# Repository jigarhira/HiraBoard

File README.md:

# HiraBoard
Custom keyboard design based on STM32 and QMK

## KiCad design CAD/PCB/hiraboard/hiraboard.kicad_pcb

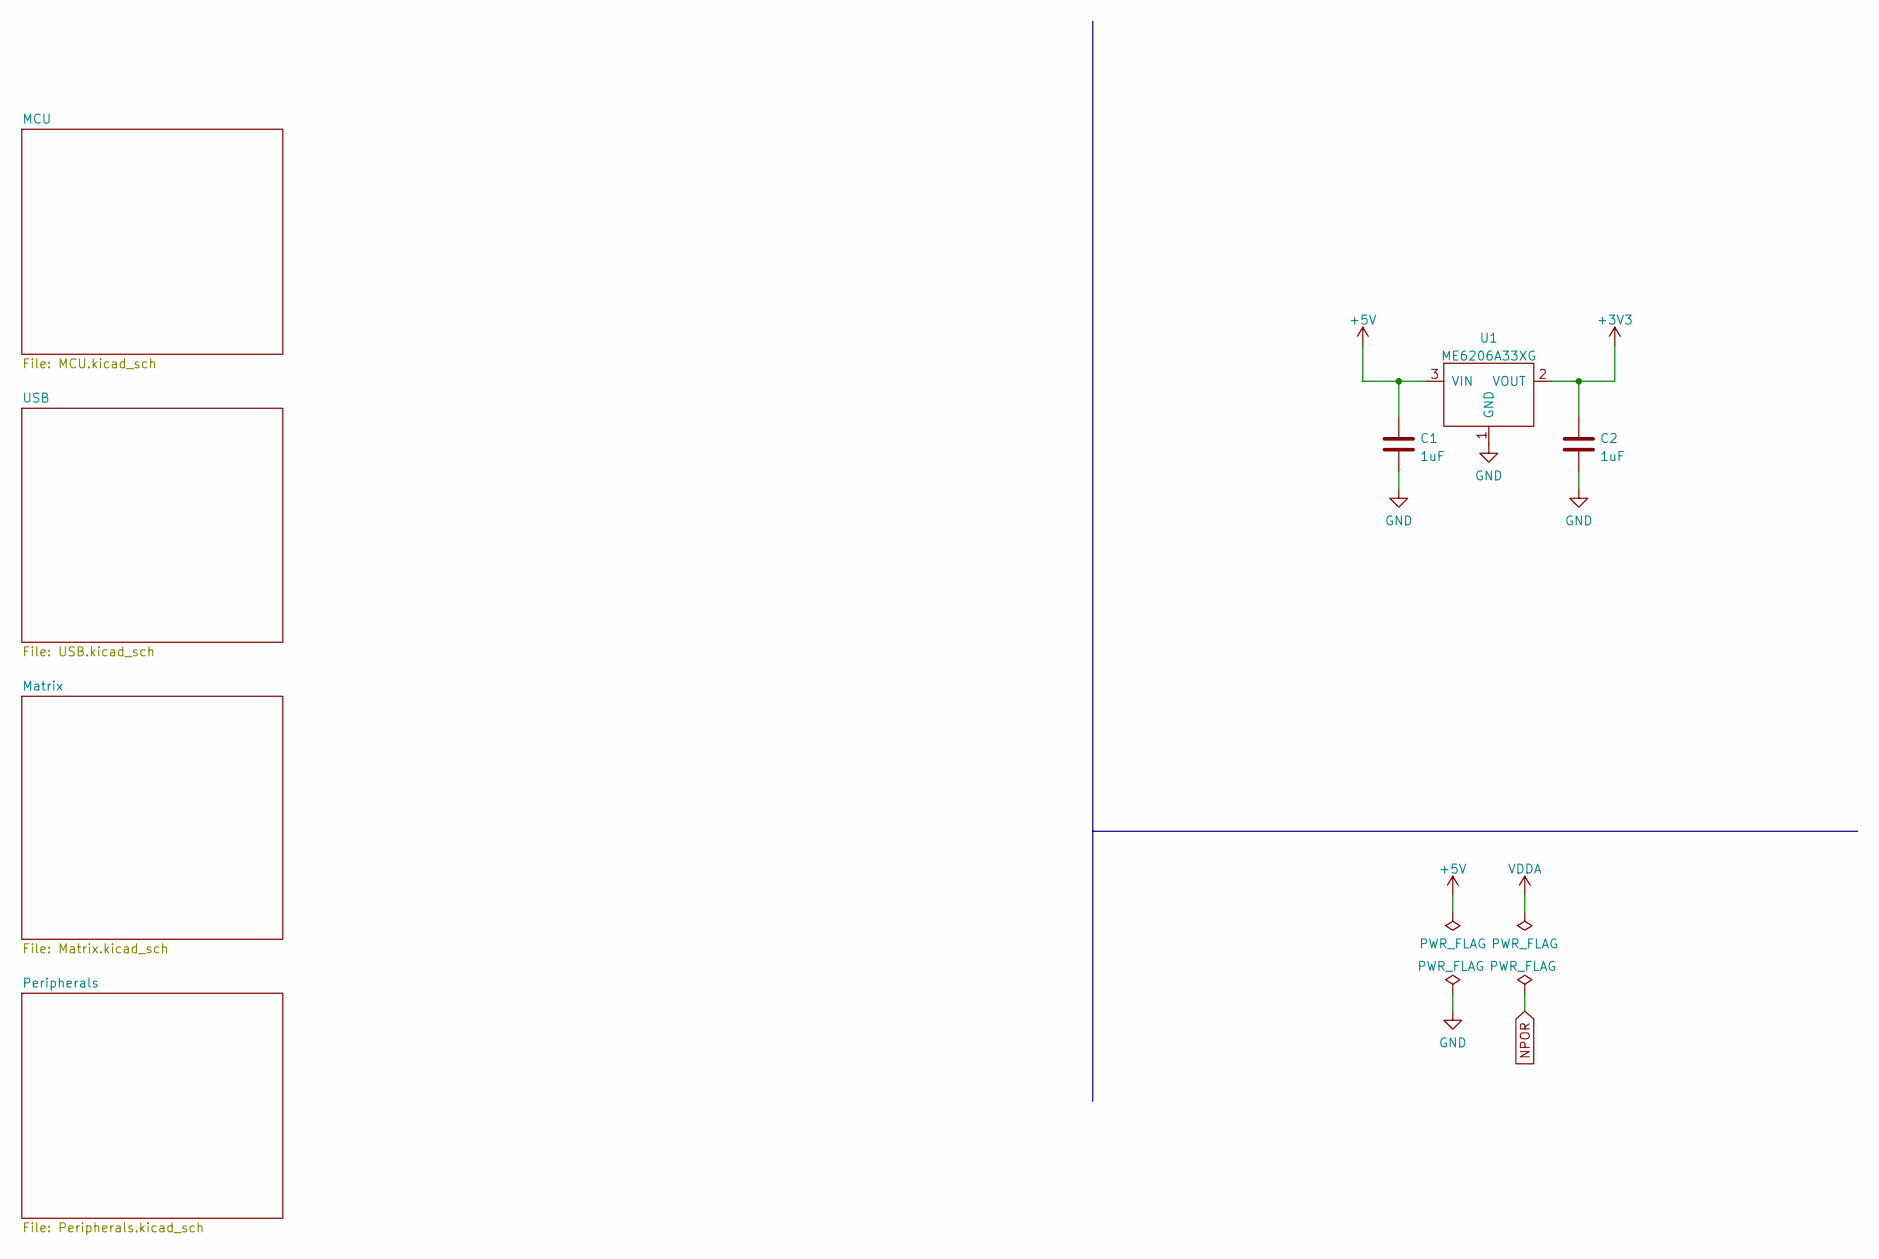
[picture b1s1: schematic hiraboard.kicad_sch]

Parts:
C1, C2: 1uF; C_0603_1608Metric
U1: ME6206A33XG; SOT-23

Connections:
+5V: C1.1, U1.3 (VIN); also elsewhere on the board
GND: C1.2, C2.2, U1.1 (GND); also elsewhere on the board

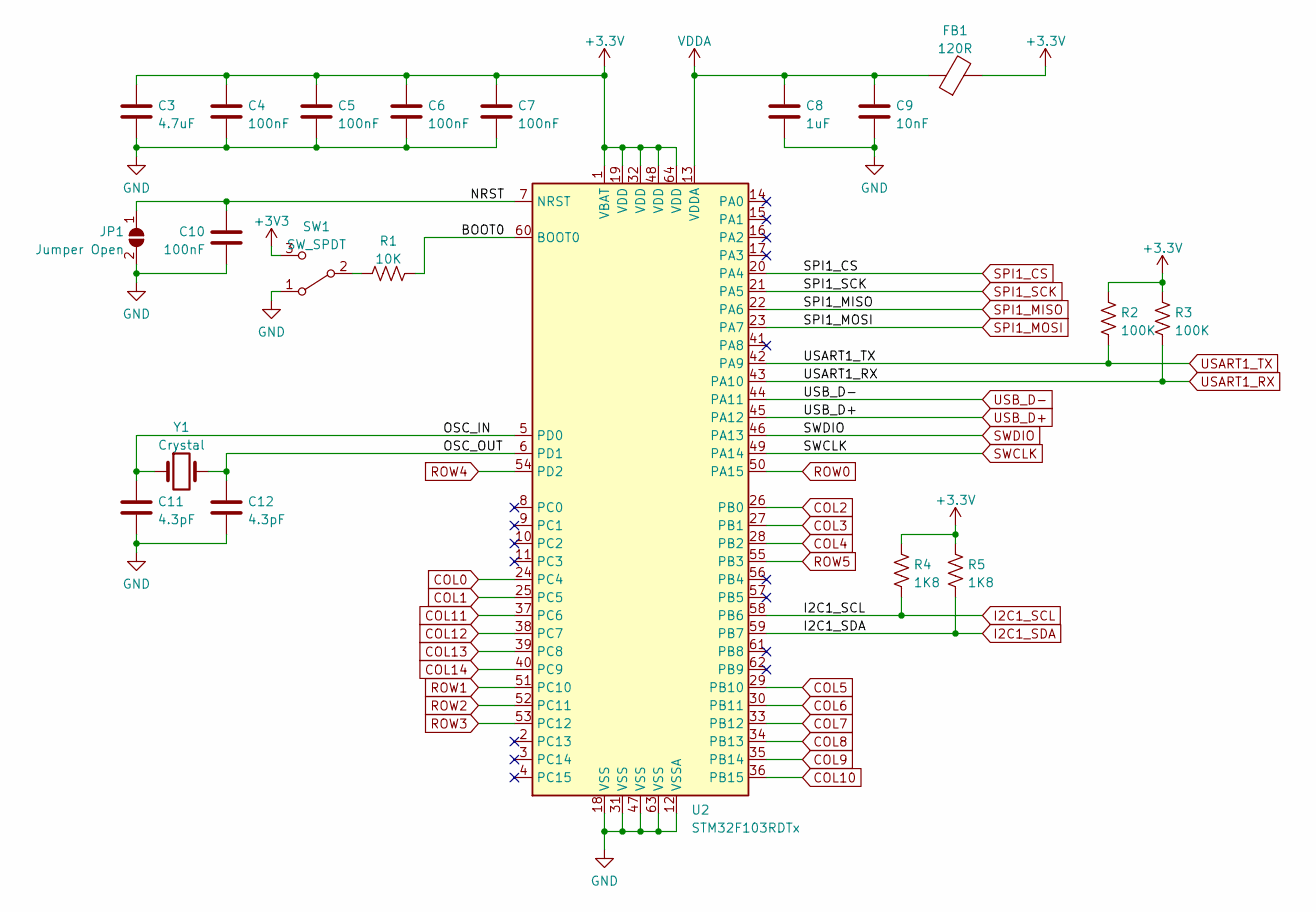
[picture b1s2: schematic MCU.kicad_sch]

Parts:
C3: 4.7uF; C_0603_1608Metric
C4, C5, C6, C7, C10: 100nF; C_0603_1608Metric
C8: 1uF; C_0603_1608Metric
C9: 10nF; C_0603_1608Metric
C11, C12: 4.3pF; C_0603_1608Metric
FB1: 120R; R_0603_1608Metric
JP1: Jumper Open; SolderJumper-2_P1.3mm_Open_RoundedPad1.0x1.5mm
R1: 10K; R_0603_1608Metric
R2, R3: 100K; R_0603_1608Metric
R4, R5: 1K8; R_0603_1608Metric
SW1: SW_SPDT
U2: STM32F103RDTx; LQFP-64_10x10mm_P0.5mm
Y1: Crystal

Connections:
/MCU/BOOT0: R1.2, U2.60 (BOOT0)
/MCU/NRST: C10.1, JP1.1 (A), U2.7 (NRST)
/MCU/OSC_IN: C11.1, U2.5 (PD0), Y1.1
/MCU/OSC_OUT: C12.1, U2.6 (PD1), Y1.2
COL0: U2.24 (PC4); also elsewhere on the board
COL1: U2.25 (PC5); also elsewhere on the board
COL2: U2.26 (PB0); also elsewhere on the board
COL3: U2.27 (PB1); also elsewhere on the board
COL4: U2.28 (PB2); also elsewhere on the board
COL5: U2.29 (PB10); also elsewhere on the board
COL6: U2.30 (PB11); also elsewhere on the board
COL7: U2.33 (PB12); also elsewhere on the board
COL8: U2.34 (PB13); also elsewhere on the board
COL9: U2.35 (PB14); also elsewhere on the board
COL10: U2.36 (PB15); also elsewhere on the board
COL11: U2.37 (PC6); also elsewhere on the board
COL12: U2.38 (PC7); also elsewhere on the board
COL13: U2.39 (PC8); also elsewhere on the board
COL14: U2.40 (PC9); also elsewhere on the board
GND: C3.2, C4.2, C5.2, C6.2, C7.2, C8.2, C9.2, C10.2, C11.2, C12.2, JP1.2 (B), SW1.1 (A), U2.12 (VSSA), U2.18 (VSS), U2.31 (VSS), U2.47 (VSS), U2.63 (VSS); also elsewhere on the board
I2C1_SCL: R4.2, U2.58 (PB6); also elsewhere on the board
I2C1_SDA: R5.2, U2.59 (PB7); also elsewhere on the board
unnamed: R1.1, SW1.2 (B)
ROW0: U2.50 (PA15); also elsewhere on the board
ROW1: U2.51 (PC10); also elsewhere on the board
ROW2: U2.52 (PC11); also elsewhere on the board
ROW3: U2.53 (PC12); also elsewhere on the board
ROW4: U2.54 (PD2); also elsewhere on the board
ROW5: U2.55 (PB3); also elsewhere on the board
SPI1_CS: U2.20 (PA4); also elsewhere on the board
SPI1_MISO: U2.22 (PA6); also elsewhere on the board
SPI1_MOSI: U2.23 (PA7); also elsewhere on the board
SPI1_SCK: U2.21 (PA5); also elsewhere on the board
SWCLK: U2.49 (PA14); also elsewhere on the board
SWDIO: U2.46 (PA13); also elsewhere on the board
USART1_RX: R3.2, U2.43 (PA10); also elsewhere on the board
USART1_TX: R2.2, U2.42 (PA9); also elsewhere on the board
USB_D+: U2.45 (PA12); also elsewhere on the board
USB_D-: U2.44 (PA11); also elsewhere on the board
VDDA: C8.1, C9.1, FB1.1, U2.13 (VDDA)

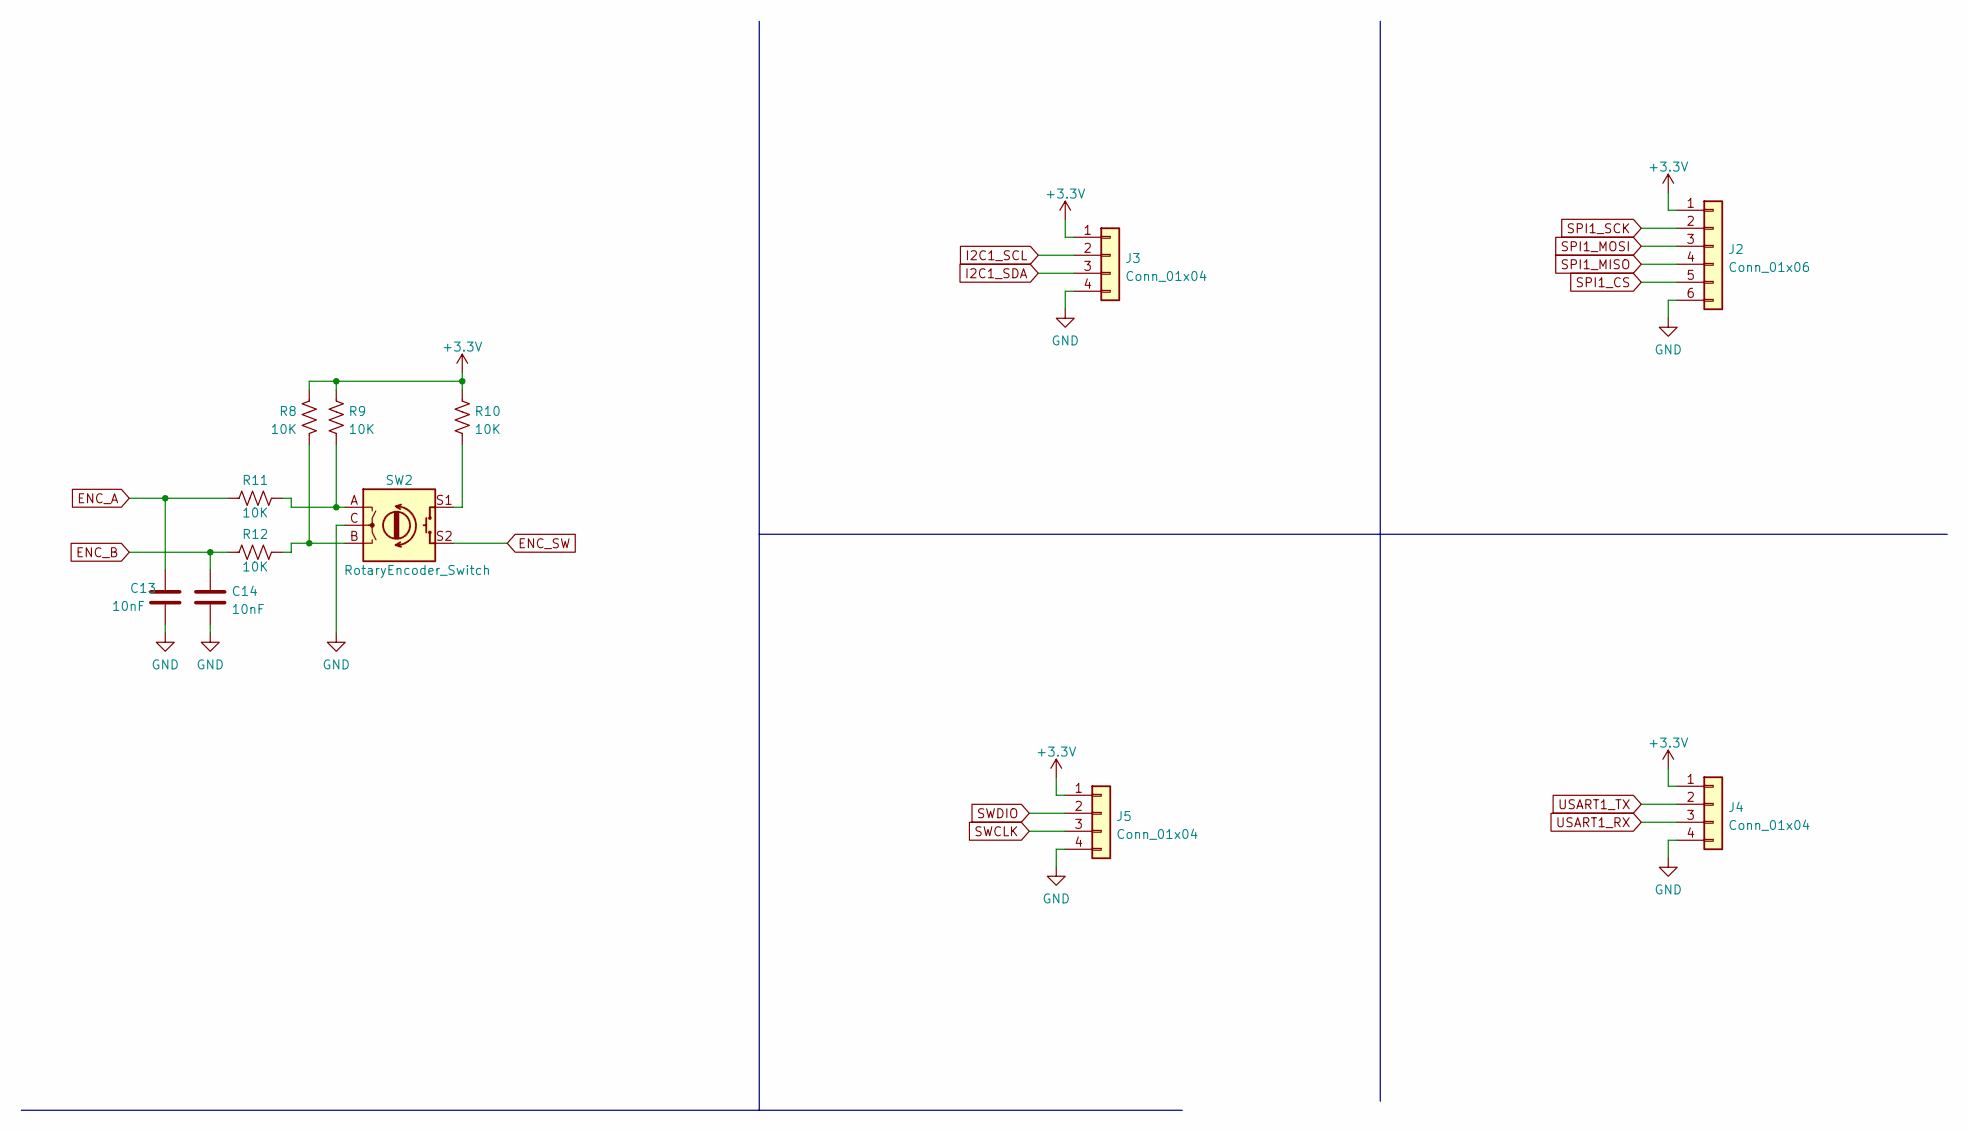
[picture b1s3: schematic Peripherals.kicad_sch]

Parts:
C13, C14: 10nF; C_0603_1608Metric
J2: Conn_01x06; PinSocket_1x06_P2.54mm_Horizontal
J3, J4, J5: Conn_01x04; PinSocket_1x04_P2.54mm_Horizontal
R8, R9, R10, R11, R12: 10K; R_0603_1608Metric
SW2: RotaryEncoder_Switch; PEC12R-4xxxF-Sxxxx

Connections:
ENC_A: C13.1, R11.2
ENC_B: C14.1, R12.2
ENC_SW: SW2.S2
GND: C13.2, C14.2, J2.6, J3.4, J4.4, J5.4, SW2.C; also elsewhere on the board
I2C1_SCL: J3.2; also elsewhere on the board
I2C1_SDA: J3.3; also elsewhere on the board
unnamed: R10.2, SW2.S1
unnamed: R9.2, R11.1, SW2.A
unnamed: R8.1, R12.1, SW2.B
SPI1_CS: J2.5; also elsewhere on the board
SPI1_MISO: J2.4; also elsewhere on the board
SPI1_MOSI: J2.3; also elsewhere on the board
SPI1_SCK: J2.2; also elsewhere on the board
SWCLK: J5.3; also elsewhere on the board
SWDIO: J5.2; also elsewhere on the board
USART1_RX: J4.3; also elsewhere on the board
USART1_TX: J4.2; also elsewhere on the board

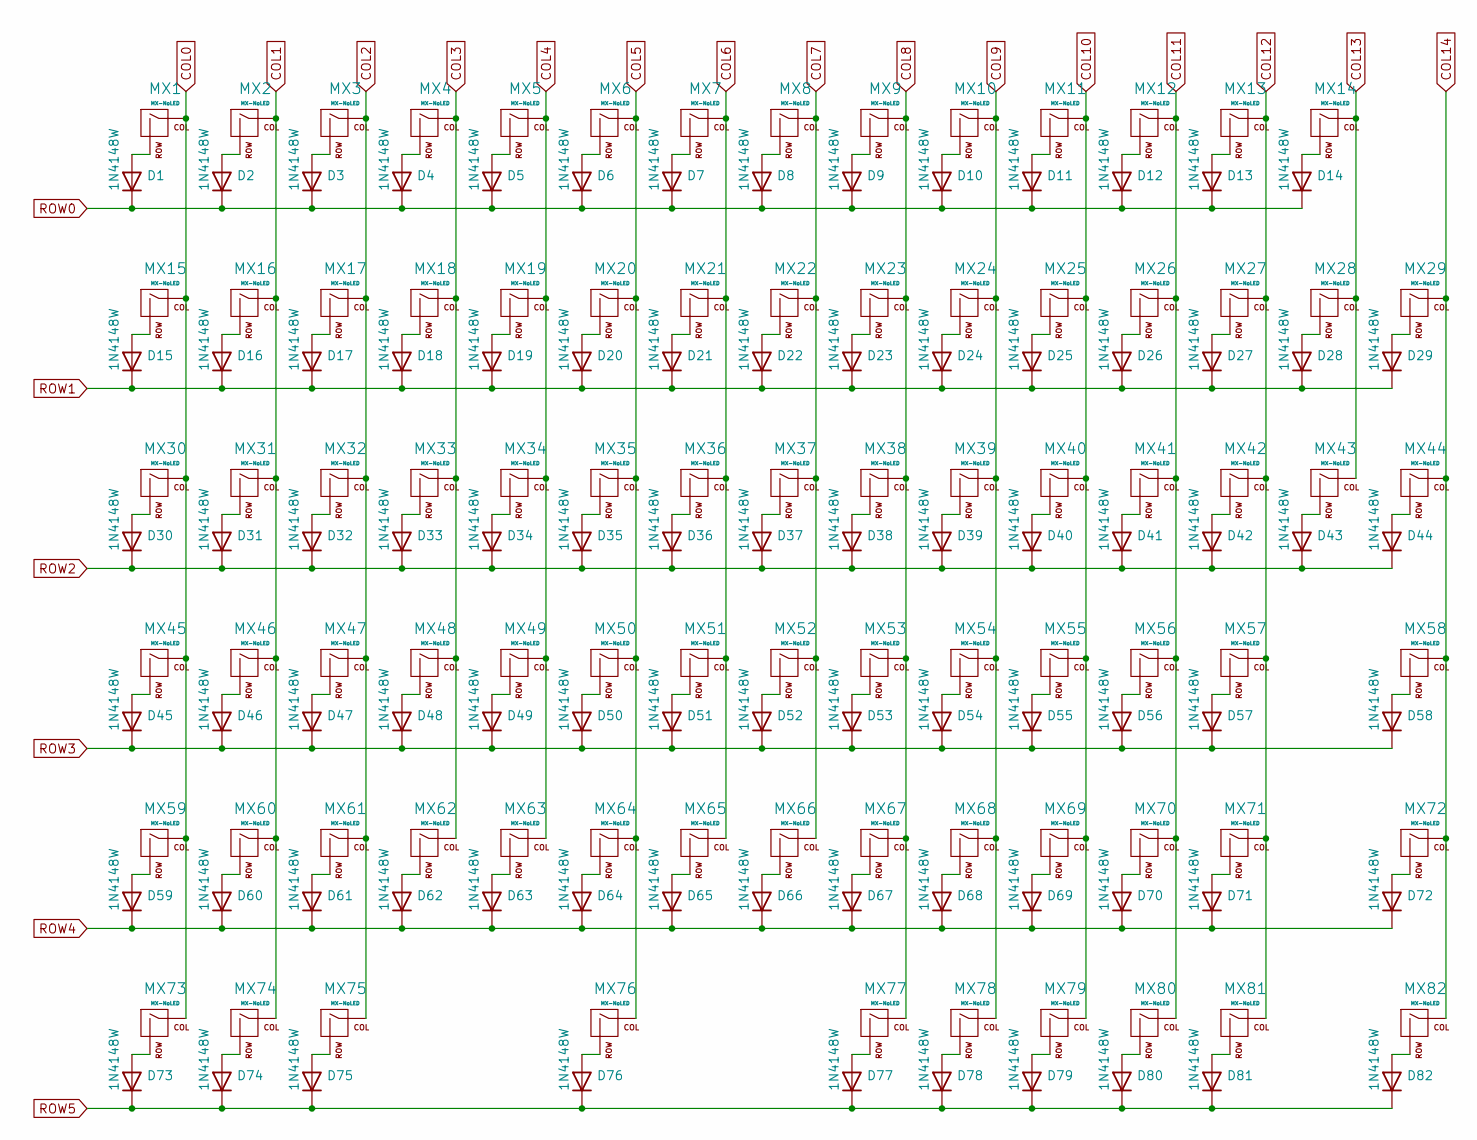
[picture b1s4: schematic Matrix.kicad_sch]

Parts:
D1, D2, D3, D4, D5, D6, D7, D8, D9, D10, D11, D12, D13, D14, D15, D16, D17, D18, D19, D20, D21, D22, D23, D24, D25, D26, D27, D28, D29, D30, D31, D32, D33, D34, D35, D36, D37, D38, D39, D40, D41, D42, D43, D44, D45, D46, D47, D48, D49, D50, D51, D52, D53, D54, D55, D56, D57, D58, D59, D60, D61, D62, D63, D64, D65, D66, D67, D68, D69, D70, D71, D72, D73, D74, D75, D76, D77, D78, D79, D80, D81, D82: 1N4148W; D_SOD-123
MX1, MX2, MX3, MX4, MX5, MX6, MX7, MX8, MX9, MX10, MX11, MX12, MX13, MX14, MX15, MX16, MX17, MX18, MX19, MX20, MX21, MX22, MX23, MX24, MX25, MX26, MX27, MX29, MX31, MX32, MX33, MX34, MX35, MX36, MX37, MX38, MX39, MX40, MX41, MX42, MX44, MX46, MX47, MX48, MX49, MX50, MX51, MX52, MX53, MX54, MX55, MX56, MX58, MX60, MX61, MX62, MX63, MX64, MX65, MX66, MX67, MX68, MX69, MX71, MX72, MX77, MX78, MX79, MX80, MX81, MX82: MX-NoLED; MXOnly-1U-Hotswap
MX28: MX-NoLED; MXOnly-2U-Hotswap
MX30, MX43: MX-NoLED; MXOnly-1.5U-Hotswap
MX45, MX70: MX-NoLED; MXOnly-1.75U-Hotswap
MX57, MX59: MX-NoLED; MXOnly-2.25U-Hotswap
MX73, MX74, MX75: MX-NoLED; MXOnly-1.25U-Hotswap
MX76: MX-NoLED; MXOnly-6.25U-Hotswap

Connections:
COL0: MX1.1 (COL), MX15.1 (COL), MX30.1 (COL), MX45.1 (COL), MX59.1 (COL), MX73.1 (COL); also elsewhere on the board
COL1: MX2.1 (COL), MX16.1 (COL), MX31.1 (COL), MX46.1 (COL), MX60.1 (COL), MX74.1 (COL); also elsewhere on the board
COL2: MX3.1 (COL), MX17.1 (COL), MX32.1 (COL), MX47.1 (COL), MX61.1 (COL), MX75.1 (COL); also elsewhere on the board
COL3: MX4.1 (COL), MX18.1 (COL), MX33.1 (COL), MX48.1 (COL), MX62.1 (COL); also elsewhere on the board
COL4: MX5.1 (COL), MX19.1 (COL), MX34.1 (COL), MX49.1 (COL), MX63.1 (COL); also elsewhere on the board
COL5: MX6.1 (COL), MX20.1 (COL), MX35.1 (COL), MX50.1 (COL), MX64.1 (COL), MX76.1 (COL); also elsewhere on the board
COL6: MX7.1 (COL), MX21.1 (COL), MX36.1 (COL), MX51.1 (COL), MX65.1 (COL); also elsewhere on the board
COL7: MX8.1 (COL), MX22.1 (COL), MX37.1 (COL), MX52.1 (COL), MX66.1 (COL); also elsewhere on the board
COL8: MX9.1 (COL), MX23.1 (COL), MX38.1 (COL), MX53.1 (COL), MX67.1 (COL), MX77.1 (COL); also elsewhere on the board
COL9: MX10.1 (COL), MX24.1 (COL), MX39.1 (COL), MX54.1 (COL), MX68.1 (COL), MX78.1 (COL); also elsewhere on the board
COL10: MX11.1 (COL), MX25.1 (COL), MX40.1 (COL), MX55.1 (COL), MX69.1 (COL), MX79.1 (COL); also elsewhere on the board
COL11: MX12.1 (COL), MX26.1 (COL), MX41.1 (COL), MX56.1 (COL), MX70.1 (COL), MX80.1 (COL); also elsewhere on the board
COL12: MX13.1 (COL), MX27.1 (COL), MX42.1 (COL), MX57.1 (COL), MX71.1 (COL), MX81.1 (COL); also elsewhere on the board
COL13: MX14.1 (COL), MX28.1 (COL), MX43.1 (COL); also elsewhere on the board
COL14: MX29.1 (COL), MX44.1 (COL), MX58.1 (COL), MX72.1 (COL), MX82.1 (COL); also elsewhere on the board
unnamed: D1.2 (A), MX1.2 (ROW)
unnamed: D2.2 (A), MX2.2 (ROW)
unnamed: D3.2 (A), MX3.2 (ROW)
unnamed: D4.2 (A), MX4.2 (ROW)
unnamed: D5.2 (A), MX5.2 (ROW)
unnamed: D6.2 (A), MX6.2 (ROW)
unnamed: D7.2 (A), MX7.2 (ROW)
unnamed: D8.2 (A), MX8.2 (ROW)
unnamed: D9.2 (A), MX9.2 (ROW)
unnamed: D10.2 (A), MX10.2 (ROW)
unnamed: D11.2 (A), MX11.2 (ROW)
unnamed: D12.2 (A), MX12.2 (ROW)
unnamed: D13.2 (A), MX13.2 (ROW)
unnamed: D14.2 (A), MX14.2 (ROW)
unnamed: D15.2 (A), MX15.2 (ROW)
unnamed: D16.2 (A), MX16.2 (ROW)
unnamed: D17.2 (A), MX17.2 (ROW)
unnamed: D18.2 (A), MX18.2 (ROW)
unnamed: D19.2 (A), MX19.2 (ROW)
unnamed: D20.2 (A), MX20.2 (ROW)
unnamed: D21.2 (A), MX21.2 (ROW)
unnamed: D22.2 (A), MX22.2 (ROW)
unnamed: D23.2 (A), MX23.2 (ROW)
unnamed: D24.2 (A), MX24.2 (ROW)
unnamed: D25.2 (A), MX25.2 (ROW)
unnamed: D26.2 (A), MX26.2 (ROW)
unnamed: D27.2 (A), MX27.2 (ROW)
unnamed: D28.2 (A), MX28.2 (ROW)
unnamed: D29.2 (A), MX29.2 (ROW)
unnamed: D30.2 (A), MX30.2 (ROW)
unnamed: D31.2 (A), MX31.2 (ROW)
unnamed: D32.2 (A), MX32.2 (ROW)
unnamed: D33.2 (A), MX33.2 (ROW)
unnamed: D34.2 (A), MX34.2 (ROW)
unnamed: D35.2 (A), MX35.2 (ROW)
unnamed: D36.2 (A), MX36.2 (ROW)
unnamed: D37.2 (A), MX37.2 (ROW)
unnamed: D38.2 (A), MX38.2 (ROW)
unnamed: D39.2 (A), MX39.2 (ROW)
unnamed: D40.2 (A), MX40.2 (ROW)
unnamed: D41.2 (A), MX41.2 (ROW)
unnamed: D42.2 (A), MX42.2 (ROW)
unnamed: D43.2 (A), MX43.2 (ROW)
unnamed: D44.2 (A), MX44.2 (ROW)
unnamed: D45.2 (A), MX45.2 (ROW)
unnamed: D46.2 (A), MX46.2 (ROW)
unnamed: D47.2 (A), MX47.2 (ROW)
unnamed: D48.2 (A), MX48.2 (ROW)
unnamed: D49.2 (A), MX49.2 (ROW)
unnamed: D50.2 (A), MX50.2 (ROW)
unnamed: D51.2 (A), MX51.2 (ROW)
unnamed: D52.2 (A), MX52.2 (ROW)
unnamed: D53.2 (A), MX53.2 (ROW)
unnamed: D54.2 (A), MX54.2 (ROW)
unnamed: D55.2 (A), MX55.2 (ROW)
unnamed: D56.2 (A), MX56.2 (ROW)
unnamed: D57.2 (A), MX57.2 (ROW)
unnamed: D58.2 (A), MX58.2 (ROW)
unnamed: D59.2 (A), MX59.2 (ROW)
unnamed: D60.2 (A), MX60.2 (ROW)
unnamed: D61.2 (A), MX61.2 (ROW)
unnamed: D62.2 (A), MX62.2 (ROW)
unnamed: D63.2 (A), MX63.2 (ROW)
unnamed: D64.2 (A), MX64.2 (ROW)
unnamed: D65.2 (A), MX65.2 (ROW)
unnamed: D66.2 (A), MX66.2 (ROW)
unnamed: D67.2 (A), MX67.2 (ROW)
unnamed: D68.2 (A), MX68.2 (ROW)
unnamed: D69.2 (A), MX69.2 (ROW)
unnamed: D70.2 (A), MX70.2 (ROW)
unnamed: D71.2 (A), MX71.2 (ROW)
unnamed: D72.2 (A), MX72.2 (ROW)
unnamed: D73.2 (A), MX73.2 (ROW)
unnamed: D74.2 (A), MX74.2 (ROW)
unnamed: D75.2 (A), MX75.2 (ROW)
unnamed: D76.2 (A), MX76.2 (ROW)
unnamed: D77.2 (A), MX77.2 (ROW)
unnamed: D78.2 (A), MX78.2 (ROW)
unnamed: D79.2 (A), MX79.2 (ROW)
unnamed: D80.2 (A), MX80.2 (ROW)
unnamed: D81.2 (A), MX81.2 (ROW)
unnamed: D82.2 (A), MX82.2 (ROW)
ROW0: D1.1 (K), D2.1 (K), D3.1 (K), D4.1 (K), D5.1 (K), D6.1 (K), D7.1 (K), D8.1 (K), D9.1 (K), D10.1 (K), D11.1 (K), D12.1 (K), D13.1 (K), D14.1 (K); also elsewhere on the board
ROW1: D15.1 (K), D16.1 (K), D17.1 (K), D18.1 (K), D19.1 (K), D20.1 (K), D21.1 (K), D22.1 (K), D23.1 (K), D24.1 (K), D25.1 (K), D26.1 (K), D27.1 (K), D28.1 (K), D29.1 (K); also elsewhere on the board
ROW2: D30.1 (K), D31.1 (K), D32.1 (K), D33.1 (K), D34.1 (K), D35.1 (K), D36.1 (K), D37.1 (K), D38.1 (K), D39.1 (K), D40.1 (K), D41.1 (K), D42.1 (K), D43.1 (K), D44.1 (K); also elsewhere on the board
ROW3: D45.1 (K), D46.1 (K), D47.1 (K), D48.1 (K), D49.1 (K), D50.1 (K), D51.1 (K), D52.1 (K), D53.1 (K), D54.1 (K), D55.1 (K), D56.1 (K), D57.1 (K), D58.1 (K); also elsewhere on the board
ROW4: D59.1 (K), D60.1 (K), D61.1 (K), D62.1 (K), D63.1 (K), D64.1 (K), D65.1 (K), D66.1 (K), D67.1 (K), D68.1 (K), D69.1 (K), D70.1 (K), D71.1 (K), D72.1 (K); also elsewhere on the board
ROW5: D73.1 (K), D74.1 (K), D75.1 (K), D76.1 (K), D77.1 (K), D78.1 (K), D79.1 (K), D80.1 (K), D81.1 (K), D82.1 (K); also elsewhere on the board

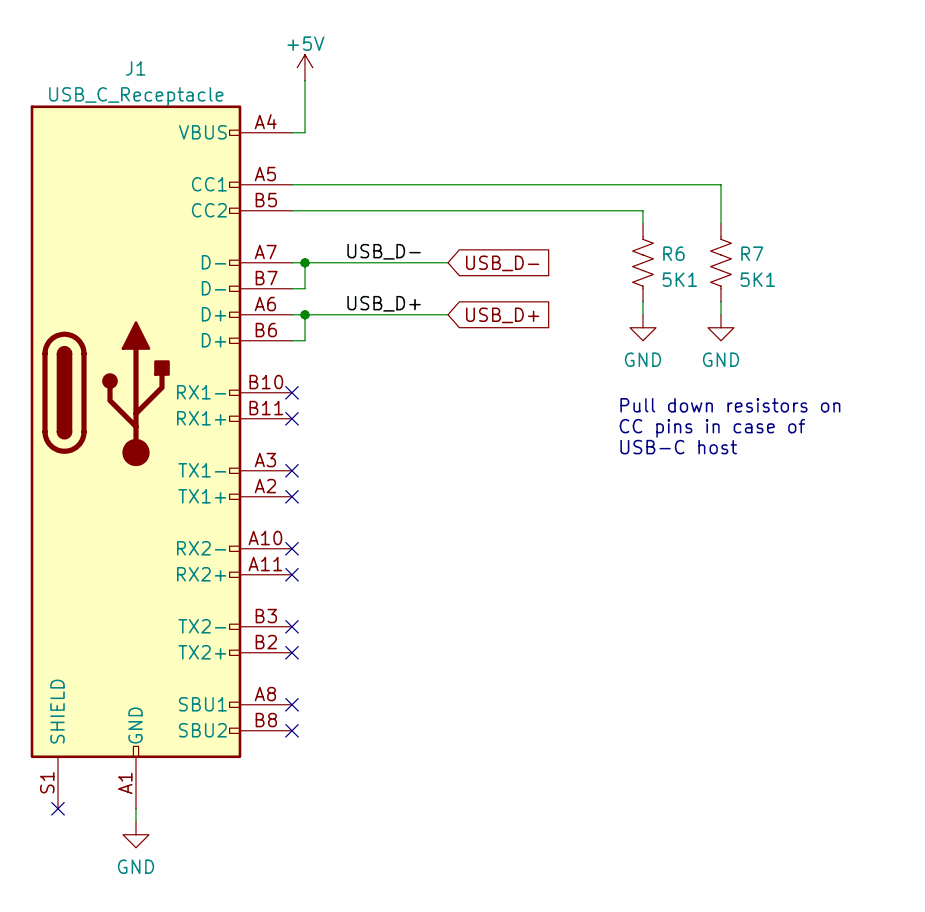
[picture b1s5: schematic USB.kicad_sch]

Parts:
J1: USB_C_Receptacle; USB_C_Receptacle_GCT_USB4085
R6, R7: 5K1; R_0603_1608Metric

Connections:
+5V: J1.A4 (VBUS), J1.A9 (VBUS), J1.B4 (VBUS), J1.B9 (VBUS); also elsewhere on the board
GND: J1.A1 (GND), J1.A12 (GND), J1.B1 (GND), J1.B12 (GND), R6.2, R7.2; also elsewhere on the board
unnamed: J1.A5 (CC1), R7.1
unnamed: J1.B5 (CC2), R6.1
USB_D+: J1.A6 (D+), J1.B6 (D+); also elsewhere on the board
USB_D-: J1.A7 (D-), J1.B7 (D-); also elsewhere on the board

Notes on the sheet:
Pull down resistors on CC pins in case of USB-C host

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
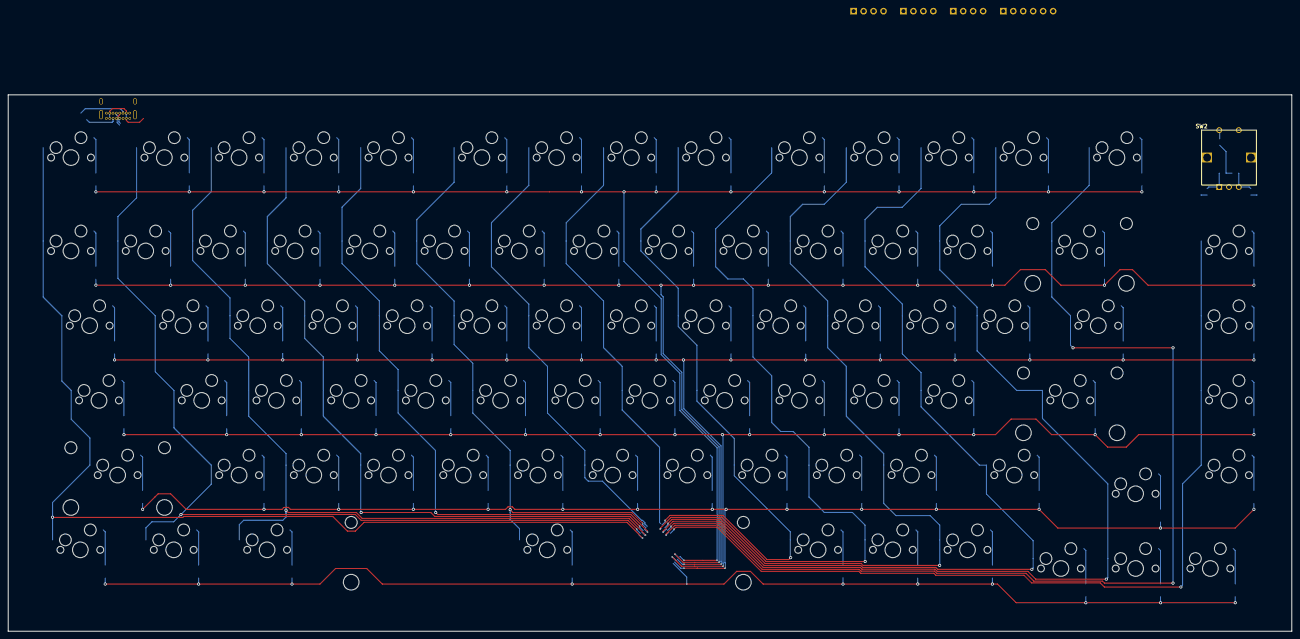
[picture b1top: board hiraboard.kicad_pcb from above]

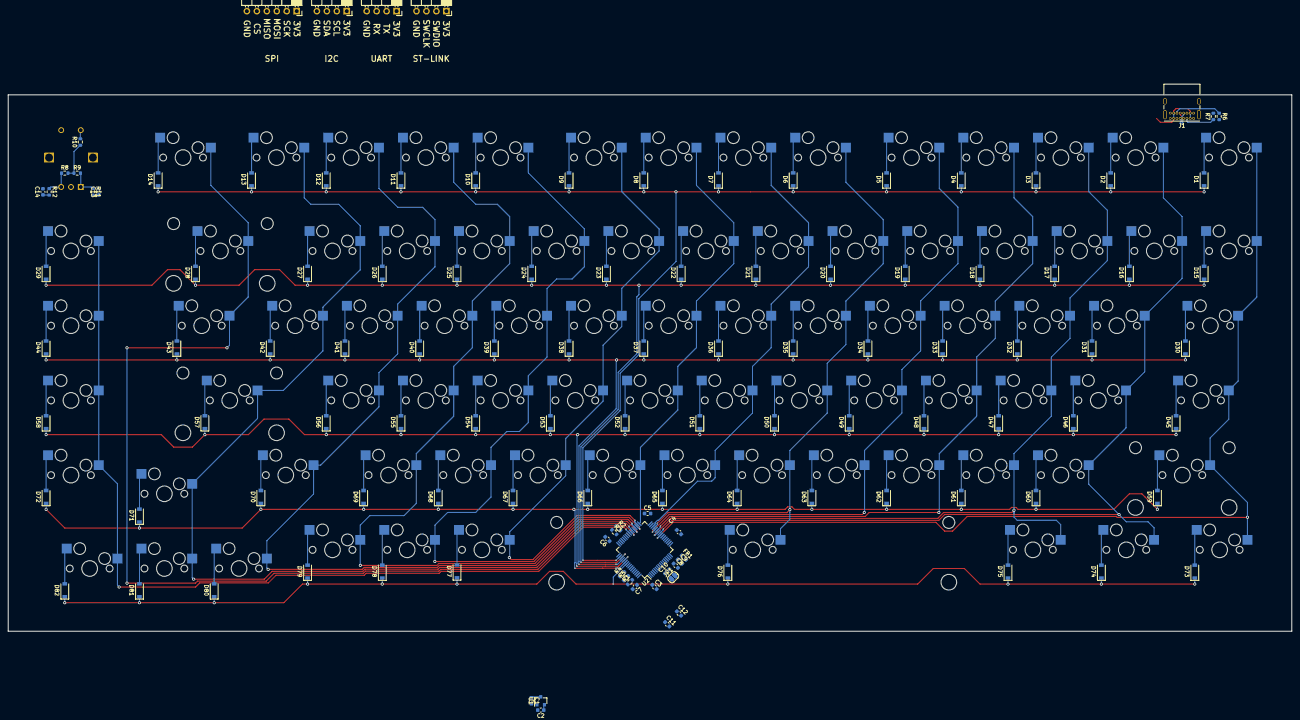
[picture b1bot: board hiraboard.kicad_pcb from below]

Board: 2 copper layers, 327.3 x 136.8 mm, 200 parts (117 on the bottom side), 130 nets.

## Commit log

2023-03-06 init commit
